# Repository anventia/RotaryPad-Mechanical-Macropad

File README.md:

# RotaryPad
Mechanical keypad with rotary encoder - PCB design files for KiCad

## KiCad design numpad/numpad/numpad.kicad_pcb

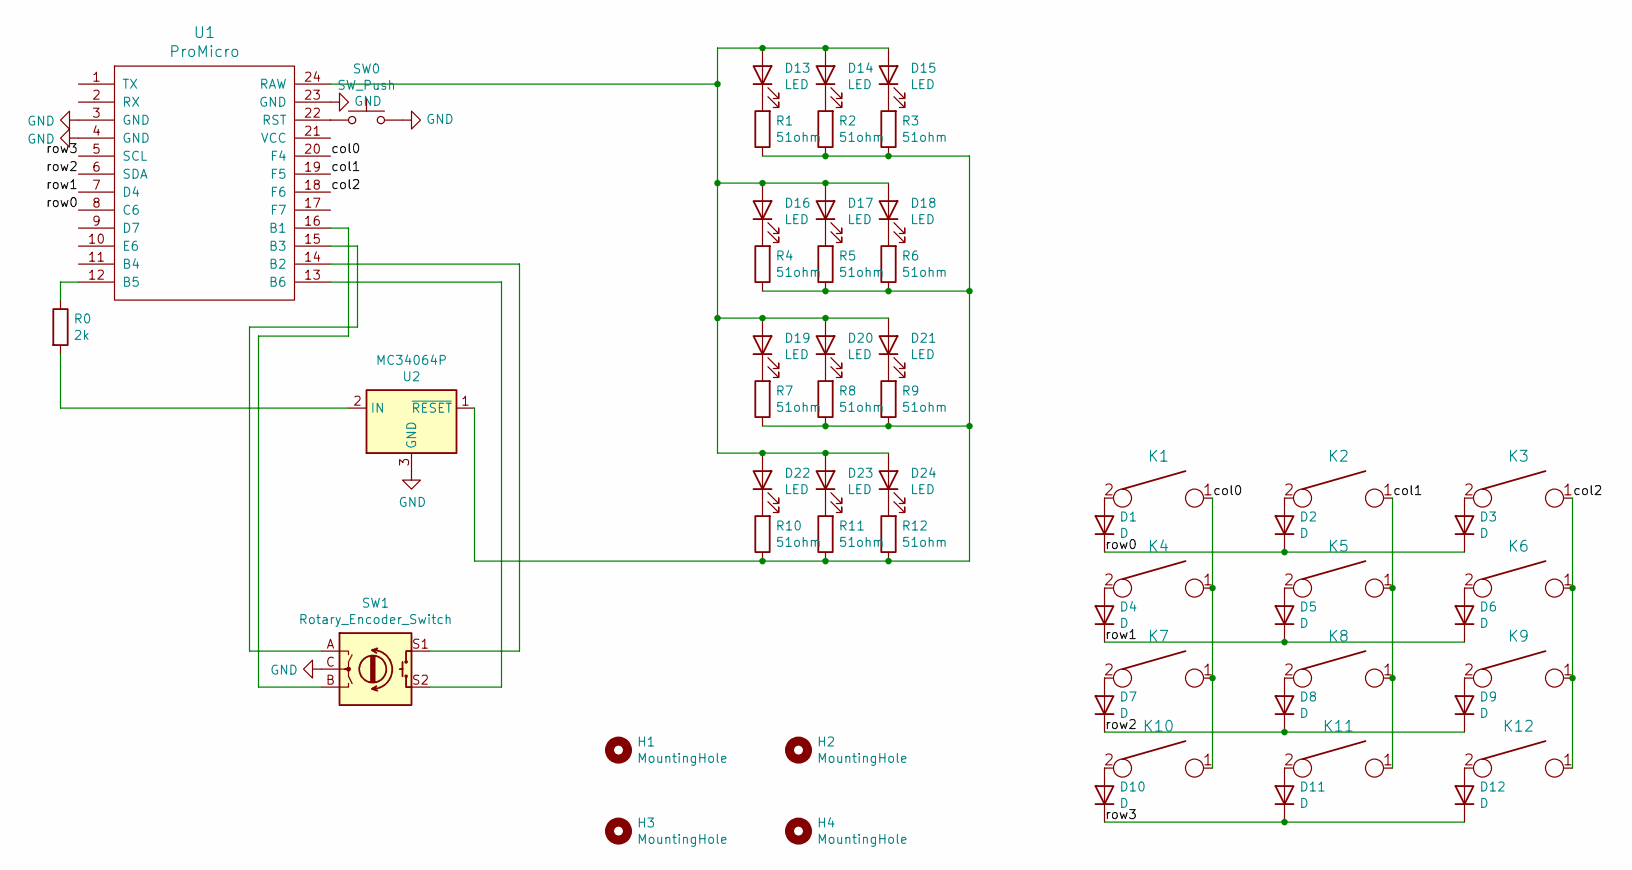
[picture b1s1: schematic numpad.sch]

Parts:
D1, D2, D3, D4, D5, D6, D7, D8, D9, D10, D11, D12: D; D_T-1_P5.08mm_Horizontal
D13, D14, D15, D16, D17, D18, D19, D20, D21, D22, D23, D24: LED; LED_D3.0mm
H1, H2, H3, H4: MountingHole; MountingHole_3.2mm_M3
K1, K2, K3, K4, K5, K6, K7, K8, K9, K10, K11, K12: KEYSW; SW_Cherry_MX_1.00u_PCB
R0: 2k; R_Axial_DIN0207_L6.3mm_D2.5mm_P7.62mm_Horizontal
R1, R2, R3, R4, R5, R6, R7, R8, R9, R10, R11, R12: 51ohm; R_Axial_DIN0207_L6.3mm_D2.5mm_P7.62mm_Horizontal
SW0: SW_Push; SW_Tactile_SKHH_Angled
SW1: Rotary_Encoder_Switch; RotaryEncoder_Alps_EC11E-Switch_Vertical_H20mm
U1: ProMicro
U2: MC34064P; TO-92L_Inline

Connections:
/col0: K1.1, K4.1, K7.1, K10.1, U1.20 (F4)
/col1: K2.1, K5.1, K8.1, K11.1, U1.19 (F5)
/col2: K3.1, K6.1, K9.1, K12.1, U1.18 (F6)
/row0: D1.1 (K), D2.1 (K), D3.1 (K), U1.8 (C6)
/row1: D4.1 (K), D5.1 (K), D6.1 (K), U1.7 (D4)
/row2: D7.1 (K), D8.1 (K), D9.1 (K), U1.6 (SDA)
/row3: D10.1 (K), D11.1 (K), D12.1 (K), U1.5 (SCL)
GND: SW0.2, SW1.C, U1.3 (GND), U1.4 (GND), U1.23 (GND), U2.3 (GND)
unnamed: D1.2 (A), K1.2
unnamed: D2.2 (A), K2.2
unnamed: D3.2 (A), K3.2
unnamed: D4.2 (A), K4.2
unnamed: D5.2 (A), K5.2
unnamed: D6.2 (A), K6.2
unnamed: D7.2 (A), K7.2
unnamed: D8.2 (A), K8.2
unnamed: D9.2 (A), K9.2
unnamed: D10.2 (A), K10.2
unnamed: D11.2 (A), K11.2
unnamed: D12.2 (A), K12.2
unnamed: D13.1 (K), R1.2
unnamed: D13.2 (A), D14.2 (A), D15.2 (A), D16.2 (A), D17.2 (A), D18.2 (A), D19.2 (A), D20.2 (A), D21.2 (A), D22.2 (A), D23.2 (A), D24.2 (A), U1.24 (RAW)
unnamed: D14.1 (K), R2.2
unnamed: D15.1 (K), R3.2
unnamed: D16.1 (K), R4.2
unnamed: D17.1 (K), R5.2
unnamed: D18.1 (K), R6.2
unnamed: D19.1 (K), R7.2
unnamed: D20.1 (K), R8.2
unnamed: D21.1 (K), R9.2
unnamed: D22.1 (K), R10.2
unnamed: D23.1 (K), R11.2
unnamed: D24.1 (K), R12.2
unnamed: R0.1, U1.12 (B5)
unnamed: R0.2, U2.2 (IN)
unnamed: R1.1, R2.1, R3.1, R4.1, R5.1, R6.1, R7.1, R8.1, R9.1, R10.1, R11.1, R12.1, U2.1 (~RESET)
unnamed: SW0.1, U1.22 (RST)
unnamed: SW1.A, U1.15 (B3)
unnamed: SW1.B, U1.16 (B1)
unnamed: SW1.S1, U1.14 (B2)
unnamed: SW1.S2, U1.13 (B6)

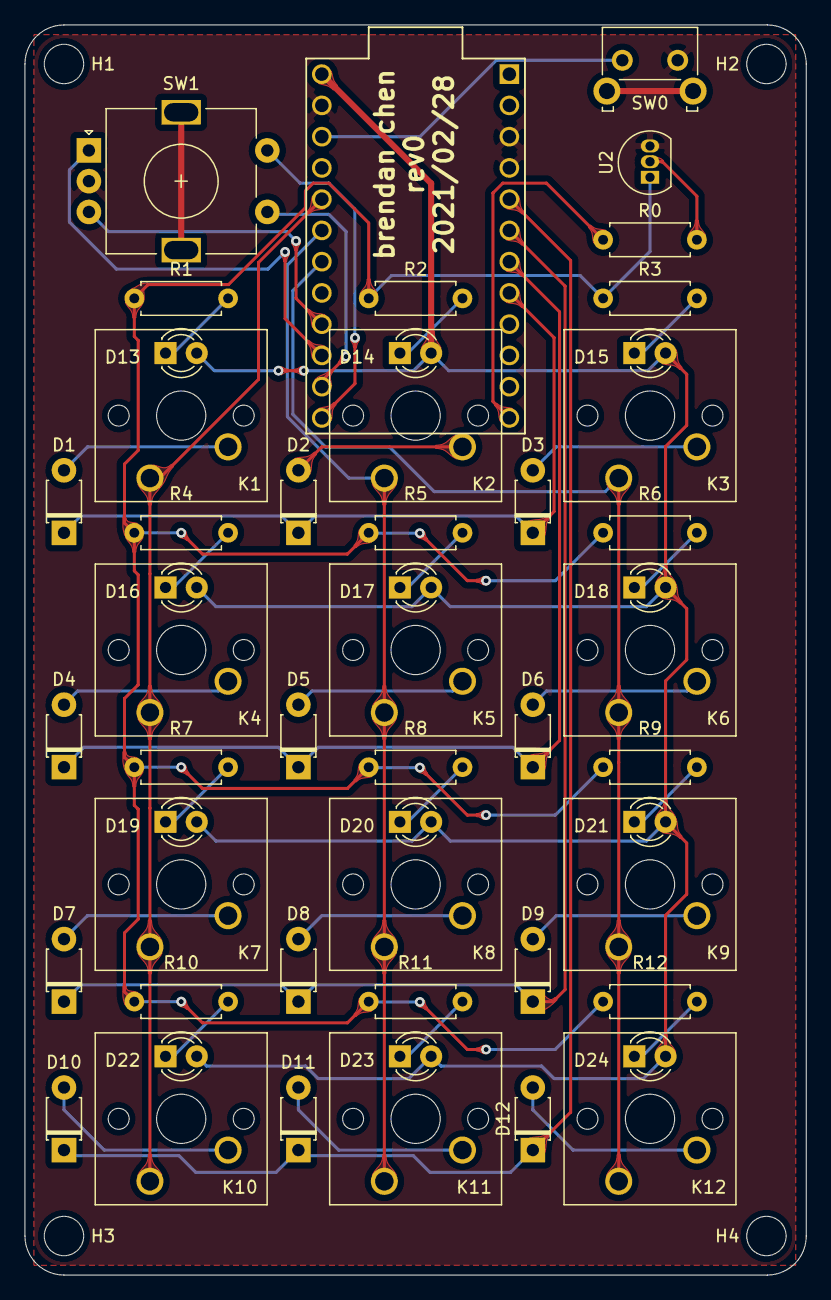
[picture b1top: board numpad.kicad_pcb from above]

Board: 2 copper layers, 63.5 x 101.6 mm, 57 parts (1 on the bottom side), 41 nets.
